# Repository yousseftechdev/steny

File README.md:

# Steny

## An open-source steno keyboard for hobbyists, powered by a Raspberry Pi Pico
Inspired by [Asterisk](https://stenokeyboards.com/products/asterisk-keyboard?srsltid=AfmBOoog4eD7K0TLSjut8bsfzl1NPyijRSejE4kbT-Yz0x29rIsmCrwi) and [YASK](https://github.com/ttempe/YASK?tab=readme-ov-file)

---

This project is a work in progress, you can check my progress and thought process over in my [JOURNAL](JOURNAL.md)

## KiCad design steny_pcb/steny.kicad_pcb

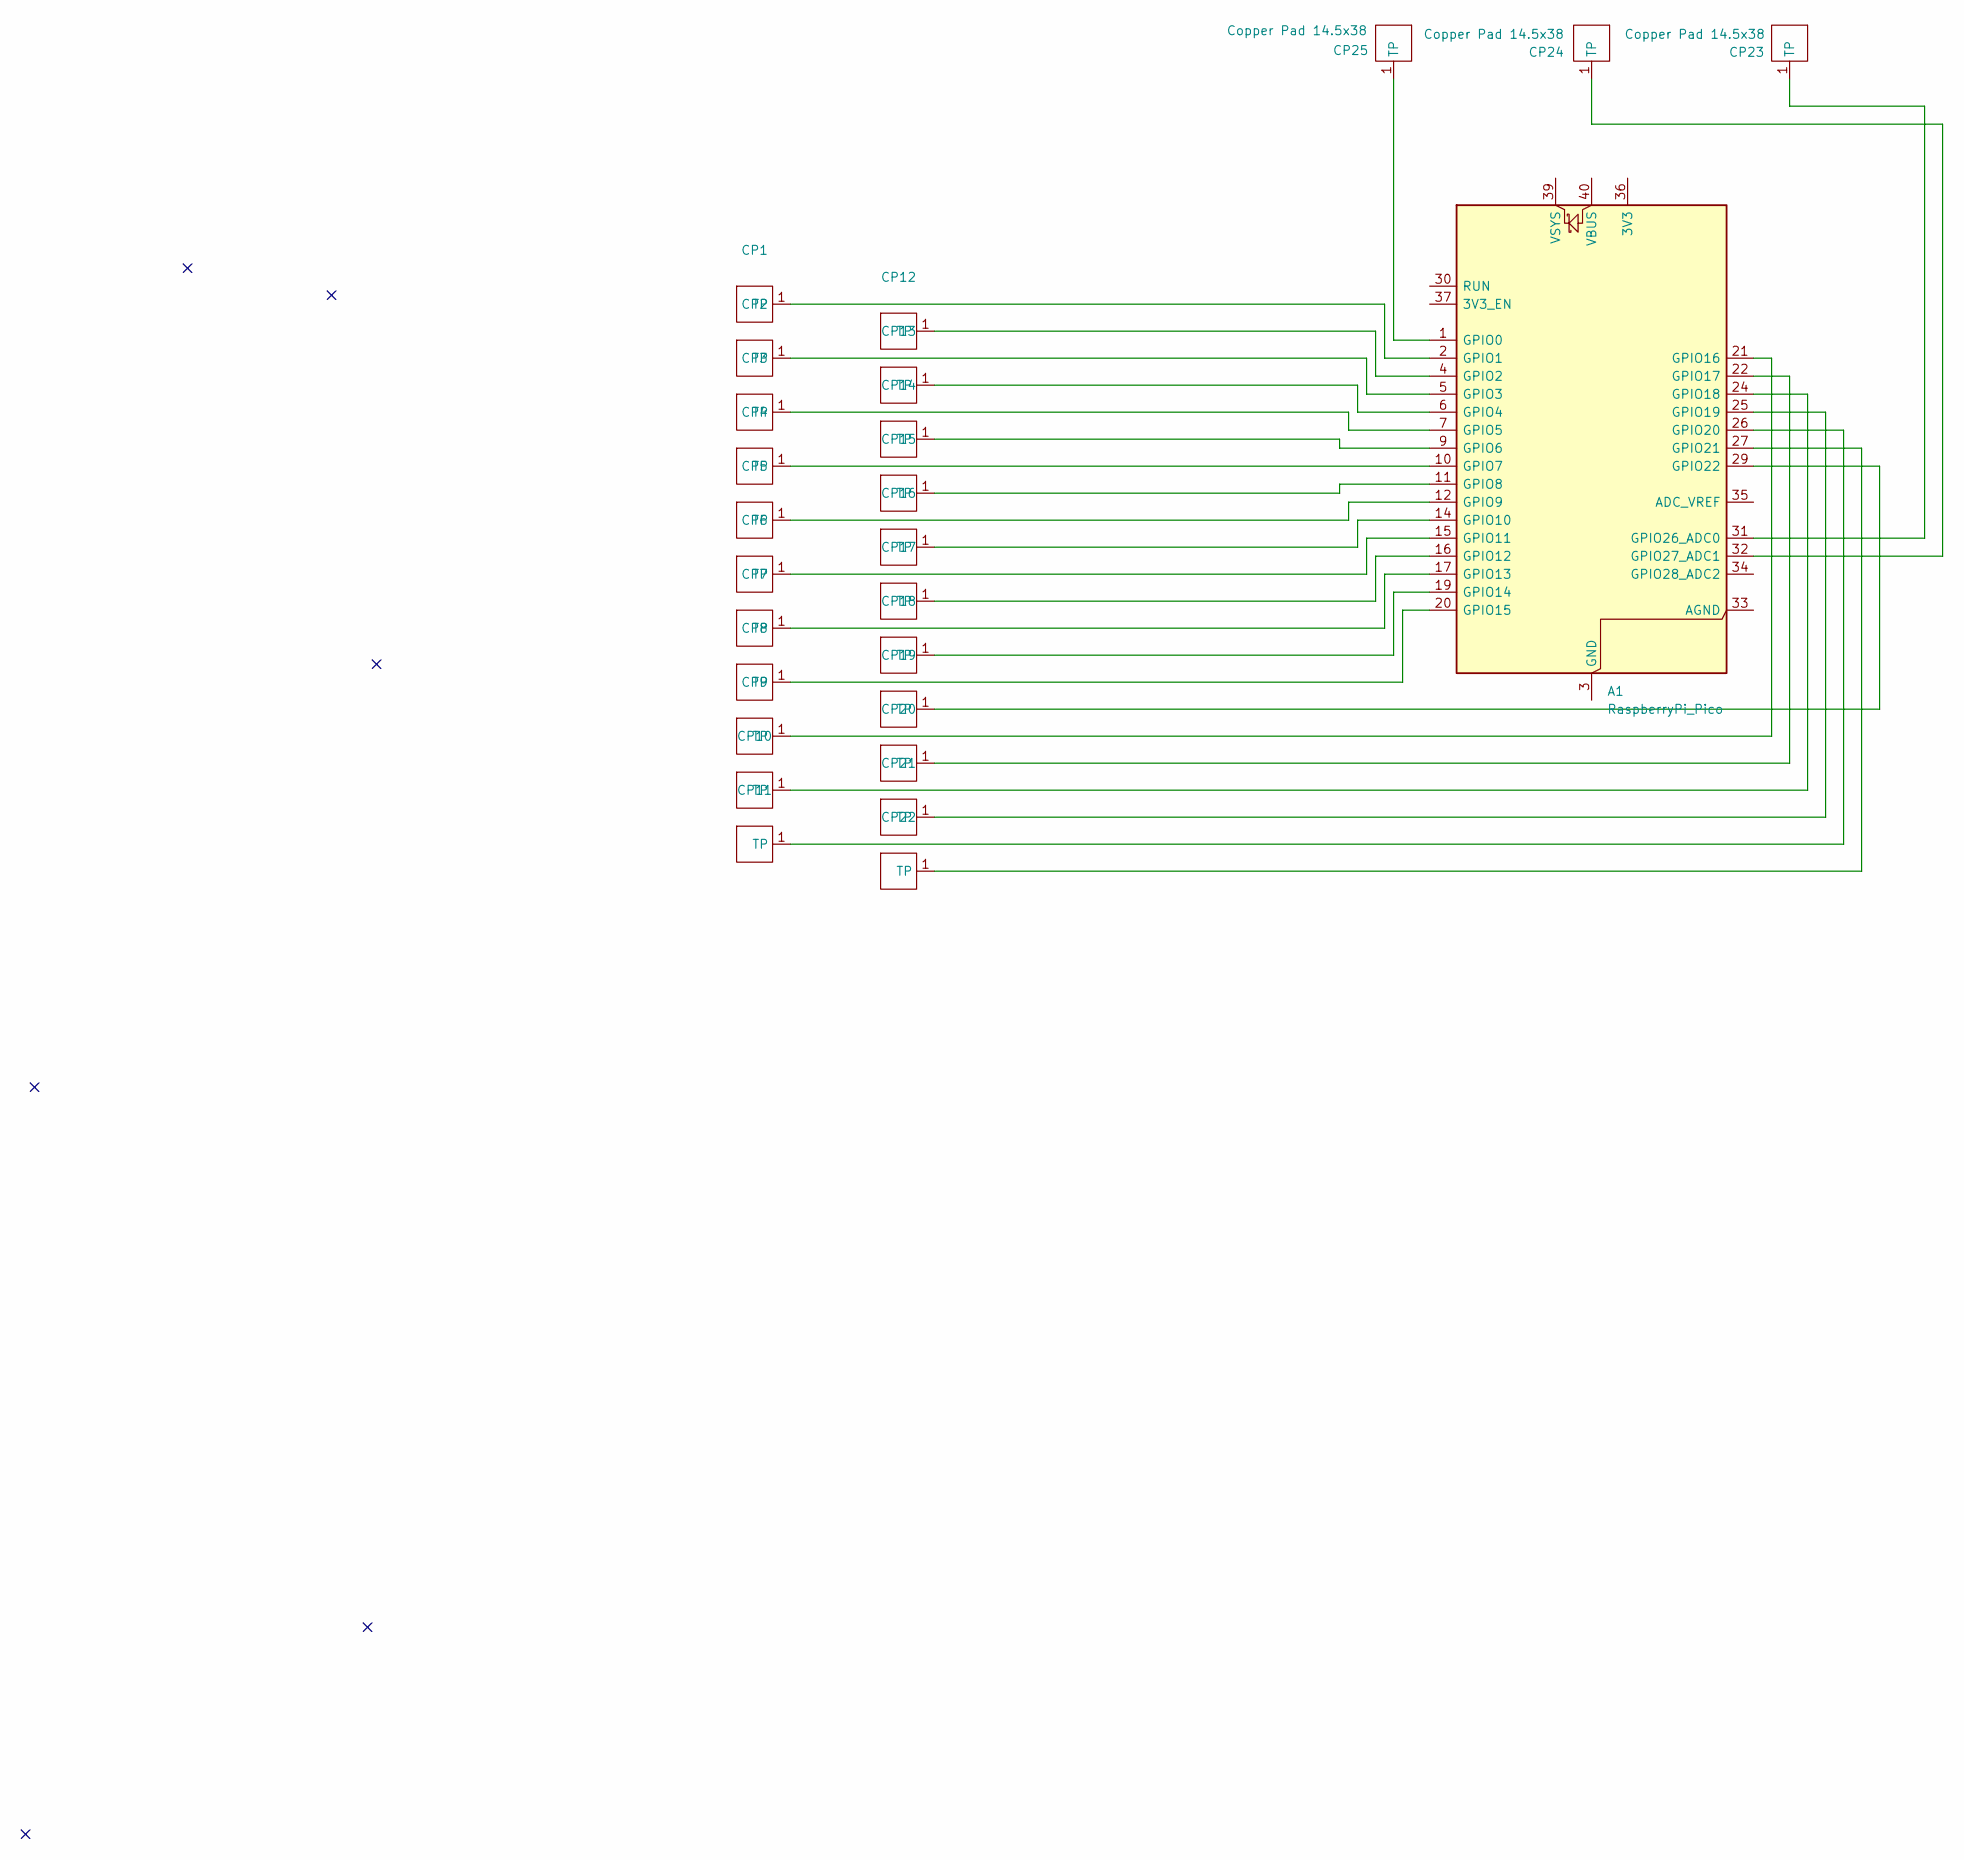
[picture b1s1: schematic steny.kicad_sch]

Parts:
A1: RaspberryPi_Pico; RaspberryPi_Pico_Common_Unspecified
CP1, CP2, CP3, CP4, CP5, CP6, CP7, CP8, CP9, CP10, CP11, CP12, CP13, CP14, CP15, CP16, CP17, CP18, CP19, CP20, CP21, CP22: Copper Pad 14.5x16.5; copper_pad_14_5x16_5
CP23, CP24, CP25: Copper Pad 14.5x38; copper_pad_14_5x38

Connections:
unnamed: A1.3 (GND), A1.8 (GND), A1.13 (GND), A1.18 (GND), A1.23 (GND), A1.28 (GND), A1.38 (GND)
unnamed: A1.1 (GPIO0), CP25.1 (TP)
unnamed: A1.2 (GPIO1), CP1.1 (TP)
unnamed: A1.4 (GPIO2), CP12.1 (TP)
unnamed: A1.5 (GPIO3), CP2.1 (TP)
unnamed: A1.6 (GPIO4), CP13.1 (TP)
unnamed: A1.7 (GPIO5), CP3.1 (TP)
unnamed: A1.9 (GPIO6), CP14.1 (TP)
unnamed: A1.10 (GPIO7), CP4.1 (TP)
unnamed: A1.11 (GPIO8), CP15.1 (TP)
unnamed: A1.12 (GPIO9), CP5.1 (TP)
unnamed: A1.14 (GPIO10), CP16.1 (TP)
unnamed: A1.15 (GPIO11), CP6.1 (TP)
unnamed: A1.16 (GPIO12), CP17.1 (TP)
unnamed: A1.17 (GPIO13), CP7.1 (TP)
unnamed: A1.19 (GPIO14), CP18.1 (TP)
unnamed: A1.20 (GPIO15), CP8.1 (TP)
unnamed: A1.21 (GPIO16), CP9.1 (TP)
unnamed: A1.22 (GPIO17), CP20.1 (TP)
unnamed: A1.24 (GPIO18), CP10.1 (TP)
unnamed: A1.25 (GPIO19), CP21.1 (TP)
unnamed: A1.26 (GPIO20), CP11.1 (TP)
unnamed: A1.27 (GPIO21), CP22.1 (TP)
unnamed: A1.29 (GPIO22), CP19.1 (TP)
unnamed: A1.31 (GPIO26_ADC0), CP23.1 (TP)
unnamed: A1.32 (GPIO27_ADC1), CP24.1 (TP)

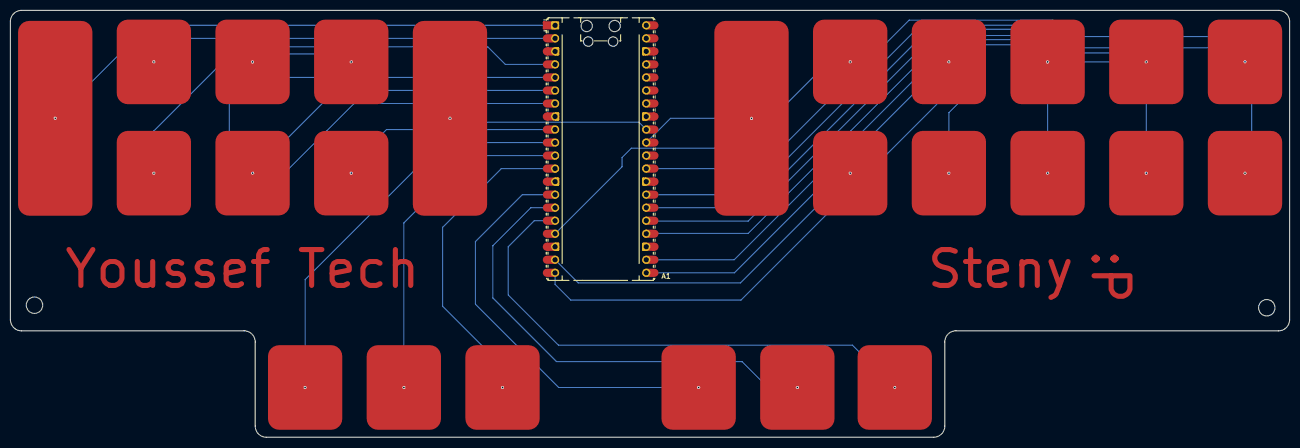
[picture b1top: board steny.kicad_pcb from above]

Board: 2 copper layers, 249.5 x 83.2 mm, 26 parts (0 on the bottom side), 26 nets.

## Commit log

2026-01-22 added basic readme layout
2026-01-22 moved pcb files to folder
2026-01-28 progress can be seen in the JOURNAL.md file.
2026-01-28 Fix image filename case in JOURNAL.md
2026-01-28 Update JOURNAL.md with image specifications
    Added width specification for images and included a new image for spacing measurement.
2026-01-28 Refactor image tags and touch pad dimensions
    Updated image syntax for measurements and adjusted dimensions for touch pads.
2026-02-01 Finished PCB
2026-02-01 added a <br> tag to push image to new line
2026-02-01 added text to the pcb
2026-02-02 started working on firmware and tests
